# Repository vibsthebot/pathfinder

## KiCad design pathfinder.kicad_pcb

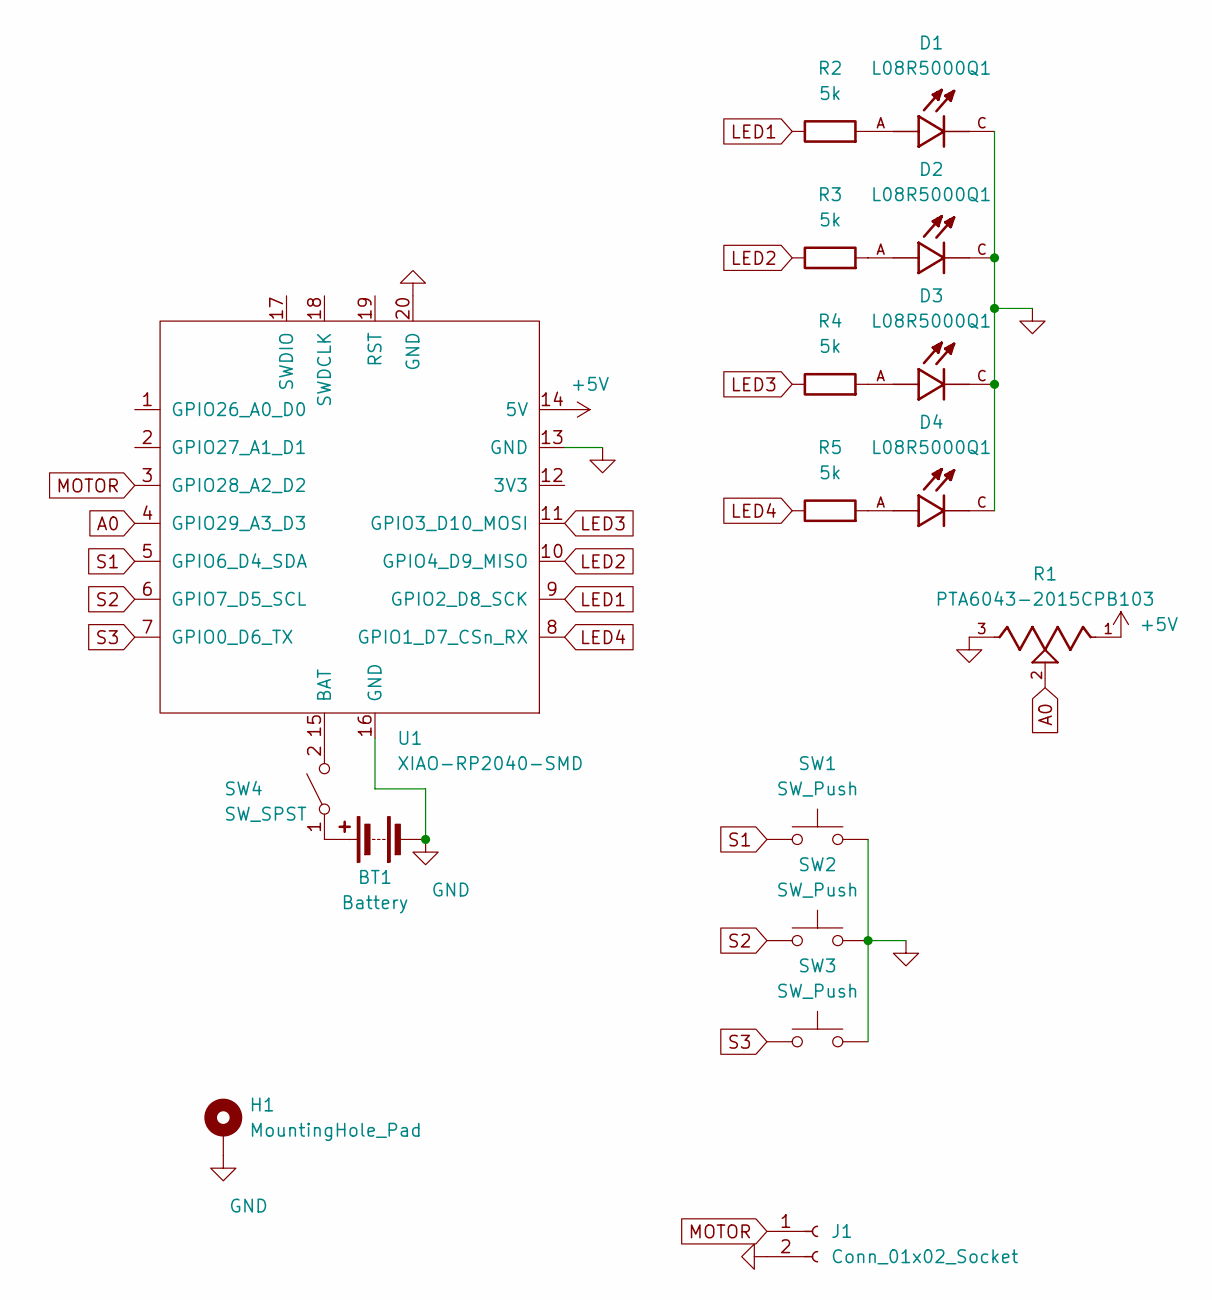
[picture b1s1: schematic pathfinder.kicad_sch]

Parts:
BT1: Battery; BatteryHolder_Keystone_2466_1xAAA
D1, D2, D3, D4: L08R5000Q1; LEDRD254W57D500H1070; PARTREV NA
H1: MountingHole_Pad; MountingHole_2.2mm_M2_DIN965_Pad
J1: Conn_01x02_Socket; PinSocket_1x02_P2.54mm_Vertical
R1: PTA6043-2015CPB103; TRIM_PTA3043-2015CPB103; PARTREV 04/21
R2, R3, R4, R5: 5k; R_Axial_DIN0204_L3.6mm_D1.6mm_P5.08mm_Horizontal
SW1, SW2, SW3: SW_Push; SW_Cherry_MX_1.00u_PCB
SW4: SW_SPST; SW_SPST_REED_CT05-XXXX-J1
U1: XIAO-RP2040-SMD

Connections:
+5V: R1.1, U1.14 (5V)
A0: R1.2, U1.4 (GPIO29_A3_D3)
GND: BT1.2 (-), D1.C, D2.C, D3.C, D4.C, H1.1, J1.2, R1.3, SW1.2, SW2.2, SW3.2, U1.13 (GND), U1.16 (GND), U1.20 (GND)
LED1: R2.1, U1.9 (GPIO2_D8_SCK)
LED2: R3.1, U1.10 (GPIO4_D9_MISO)
LED3: R4.1, U1.11 (GPIO3_D10_MOSI)
LED4: R5.1, U1.8 (GPIO1_D7_CSn_RX)
MOTOR: J1.1, U1.3 (GPIO28_A2_D2)
unnamed: BT1.1 (+), SW4.1 (A)
unnamed: D1.A, R2.2
unnamed: D2.A, R3.2
unnamed: D3.A, R4.2
unnamed: D4.A, R5.2
unnamed: SW4.2 (B), U1.15 (BAT)
S1: SW1.1, U1.5 (GPIO6_D4_SDA)
S2: SW2.1, U1.6 (GPIO7_D5_SCL)
S3: SW3.1, U1.7 (GPIO0_D6_TX)

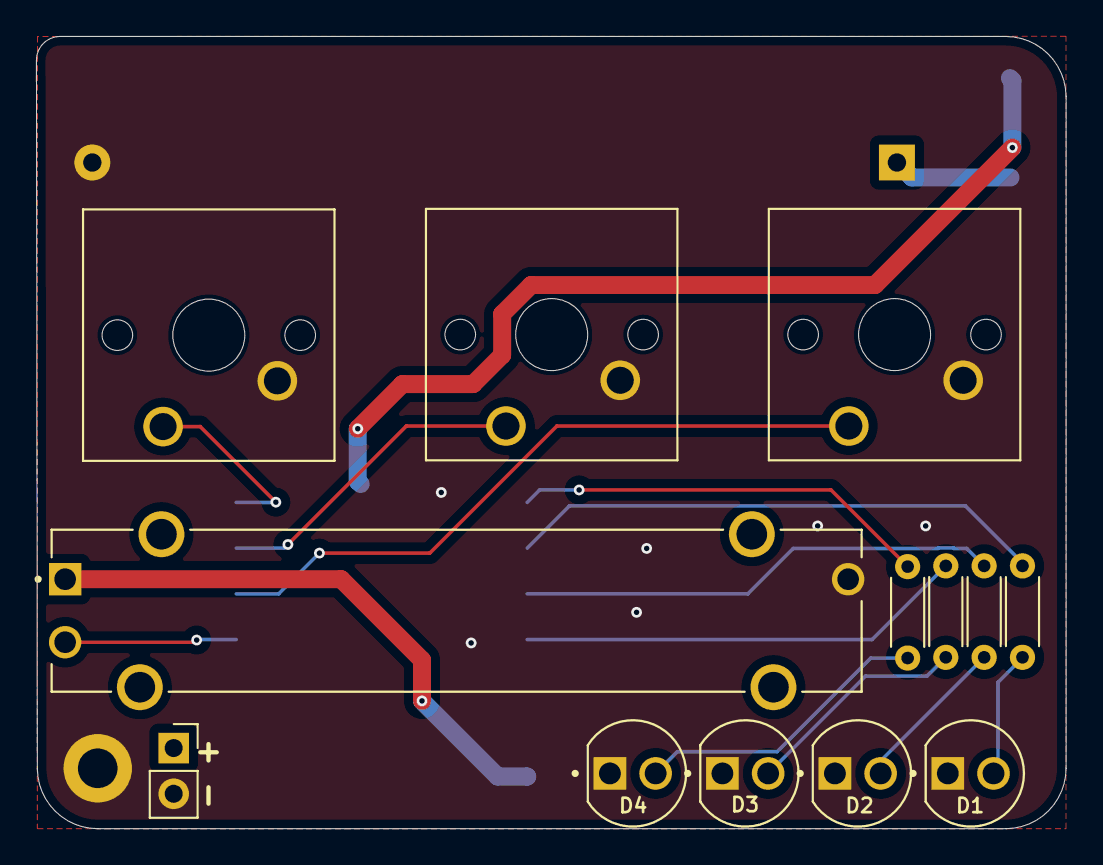
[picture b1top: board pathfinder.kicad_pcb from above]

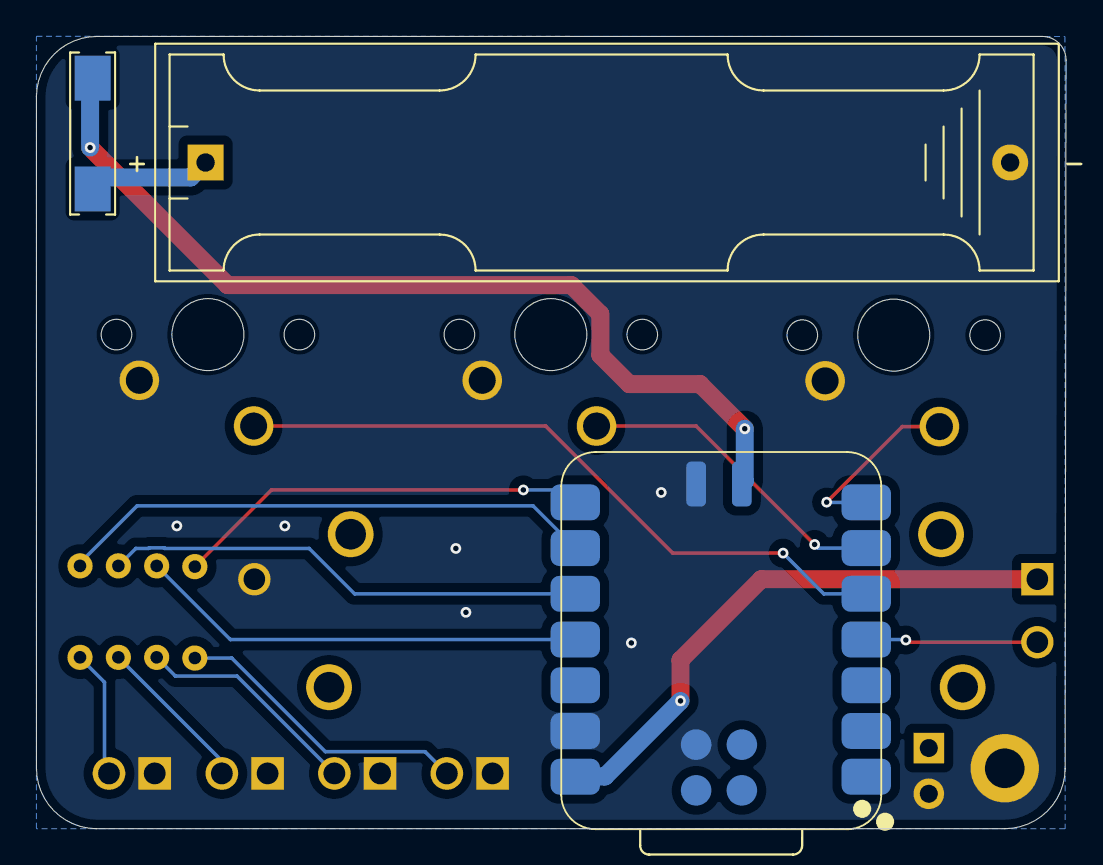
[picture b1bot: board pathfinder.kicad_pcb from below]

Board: 2 copper layers, 57.2 x 44.0 mm, 17 parts (3 on the bottom side), 17 nets.

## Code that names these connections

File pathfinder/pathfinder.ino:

int BUT1 = D4;
int BUT2 = D5;
int BUT3 = D6;


int LED1 = D8;
int LED2 = D9;
int LED3 = D10;
int LED4 = D7;
int SL = A3;
int motorPin = D2;
bool running = false;
bool paused = false;

unsigned long startMillis = 0;
unsigned long pausedMillis = 0;
unsigned long elapsedMillis = 0;

int timerDuration = 1;
int timeLeft = 1;
int slider = 1;
bool but2prev = false;
bool but1prev = false;
bool but3prev = false;

void setup() {
  pinMode(BUT1, INPUT);

  pinMode(BUT2, INPUT);

  pinMode(BUT3, INPUT);


  pinMode(LED1, OUTPUT);

  pinMode(LED2, OUTPUT);

  pinMode(LED3, OUTPUT);
}

void loop() {
  if (!running && !paused) {
    int slider = analogRead(SL);
    timerDuration = map(potValue, 0, 1023, 1, 60);
    timeLeft = timerDuration;
    Serial.print("Set timer: ");
    Serial.print(timerDuration);
    Serial.println(" minutes");
    delay(200);
  }

  if (digitalRead(BUT1) == HIGH && !running && !but1prev) {
    but1prev = true;
    running = true;
    paused = false;
    startMillis = millis();
    elapsedMillis = 0;
    timeLeft = timerDuration;
    digitalWrite(LED1, HIGH);
    digitalWrite(LED2, HIGH);
    Serial.println("Timer started!");
  }
  if (digitalRead(BUT1) == HIGH && running && !but1prev) {
    but1prev = true;
    running = false;
    paused = false;
    elapsedMillis = 0;
    timeLeft = timerDuration;
    digitalWrite(LED1, LOW);
    digitalWrite(LED2, LOW);
  }
  else if (digitalRead(BUT2) == HIGH && running && !but2prev) {
    but2prev = true;
    if (!paused) {
      paused = true;
      pausedMillis = millis();
      digitalWrite(LED2, LOW);
      Serial.println("Paused.");
    }
    else {
      paused = false;
      startMillis += (millis() - pausedMillis);
      digitalWrite(LED2, HIGH);
      Serial.println("Resumed.");
    }
  }
  
  else if (digitalRead(BUT3) == HIGH && running) {
    currentTimeSequence();
  }
  

  if (running && !paused) {
    elapsedMillis = millis() - startMillis;
    int elapsedMinutes = elapsedMillis / 60000; 
    timeLeft = timerDuration - elapsedMinutes;
    float percent = (float) (4 * timeLeft/timerDuration)/4.0;
    if (percent == 0.25 || percent > 0.5) {
      digitalWrite(LED4, HIGH);
    } else {
      digitalWrite(LED4, LOW);
    }
    if (percent > 0.25) {
      digitalWrite(LED3, HIGH);
    } else {
      digitalWrite(LED3, LOW);
    }

    if (timeLeft <= 0) {
      running = false;
      ledSequenceAfterTimer();
      digitalWrite(LED1, LOW);
      digitalWrite(LED2, HIGH);
      Serial.println("Timer finished!");
    }
  } else {
    digitalWrite(LED1, LOW);
    digitalWrite(LED2, LOW);
  }
  if (digitalRead(BUT2) == LOW) {
    but2prev = false;
  }
  if (digitalRead(BUT1) == LOW) {
    but1prev = false;
  }
}

void ledSequenceAfterTimer() {
  unsigned long startTime = millis();
  while (millis() - startTime < 5000) {
    digitalWrite(LED1, HIGH);
    digitalWrite(LED2, LOW);
    delay(500);

    digitalWrite(LED1, LOW);
    digitalWrite(LED2, HIGH);
    delay(500);
  }
}

void currentTimeSequence() {
  unsigned long startTime = millis();
  int first = timeLeft / 15;
  int second = (timeLeft - first * 15) / 5;
  int third = (timeLeft - first * 15 - second * 5);
  digitalWrite(LED1, (first > 3) ? HIGH : LOW);
  digitalWrite(LED2, (first > 2) ? HIGH : LOW);
  digitalWrite(LED3, (first > 1) ? HIGH : LOW);
  digitalWrite(LED4, (first > 0) ? HIGH : LOW);
  digitalWrite(motorPin, HIGH); 
  delay(500);

  digitalWrite(LED1, (second > 3) ? HIGH : LOW);
  digitalWrite(LED2, (second > 2) ? HIGH : LOW);
  digitalWrite(LED3, (second > 1) ? HIGH : LOW);
  digitalWrite(LED4, (second > 0) ? HIGH : LOW);
  delay(250);

  digitalWrite(motorPin, LOW);
  delay(250);

  digitalWrite(motorPin, HIGH);
  digitalWrite(LED1, (third > 3) ? HIGH : LOW);
  digitalWrite(LED2, (third > 2) ? HIGH : LOW);
  digitalWrite(LED3, (third > 1) ? HIGH : LOW);
  digitalWrite(LED4, (third > 0) ? HIGH : LOW);
  delay(500);
  digitalWrite(motorPin, LOW);

  }
}

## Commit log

2025-07-04 Finished pcb
2025-07-04 Finished arduino code
2025-07-04 pcb + drill files, blender file
2025-08-09 cleaned up schematic a tiny bit
